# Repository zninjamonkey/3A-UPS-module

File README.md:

# 3A-UPS-module
made for hack club half life in 1 week. cut me some slack

This is supposed to be a UPS (uninterruptible power supply) module to power portable diy electronics projects.

It was inspired by the adafruit powerboost 1000c, but I wanted usb C connection and to be able to provide higher current to power devices such as a rapsberry pi.

It uses a BQ25306 for battery charging and load sharing, and a TPS61089 to boost the lithium ion battery to a 5V output. both chips are by Texas instruments. 

**kicad render**

<br>
**schematic**

<br>

I have not actually built this yet so I'm not sure if it even works

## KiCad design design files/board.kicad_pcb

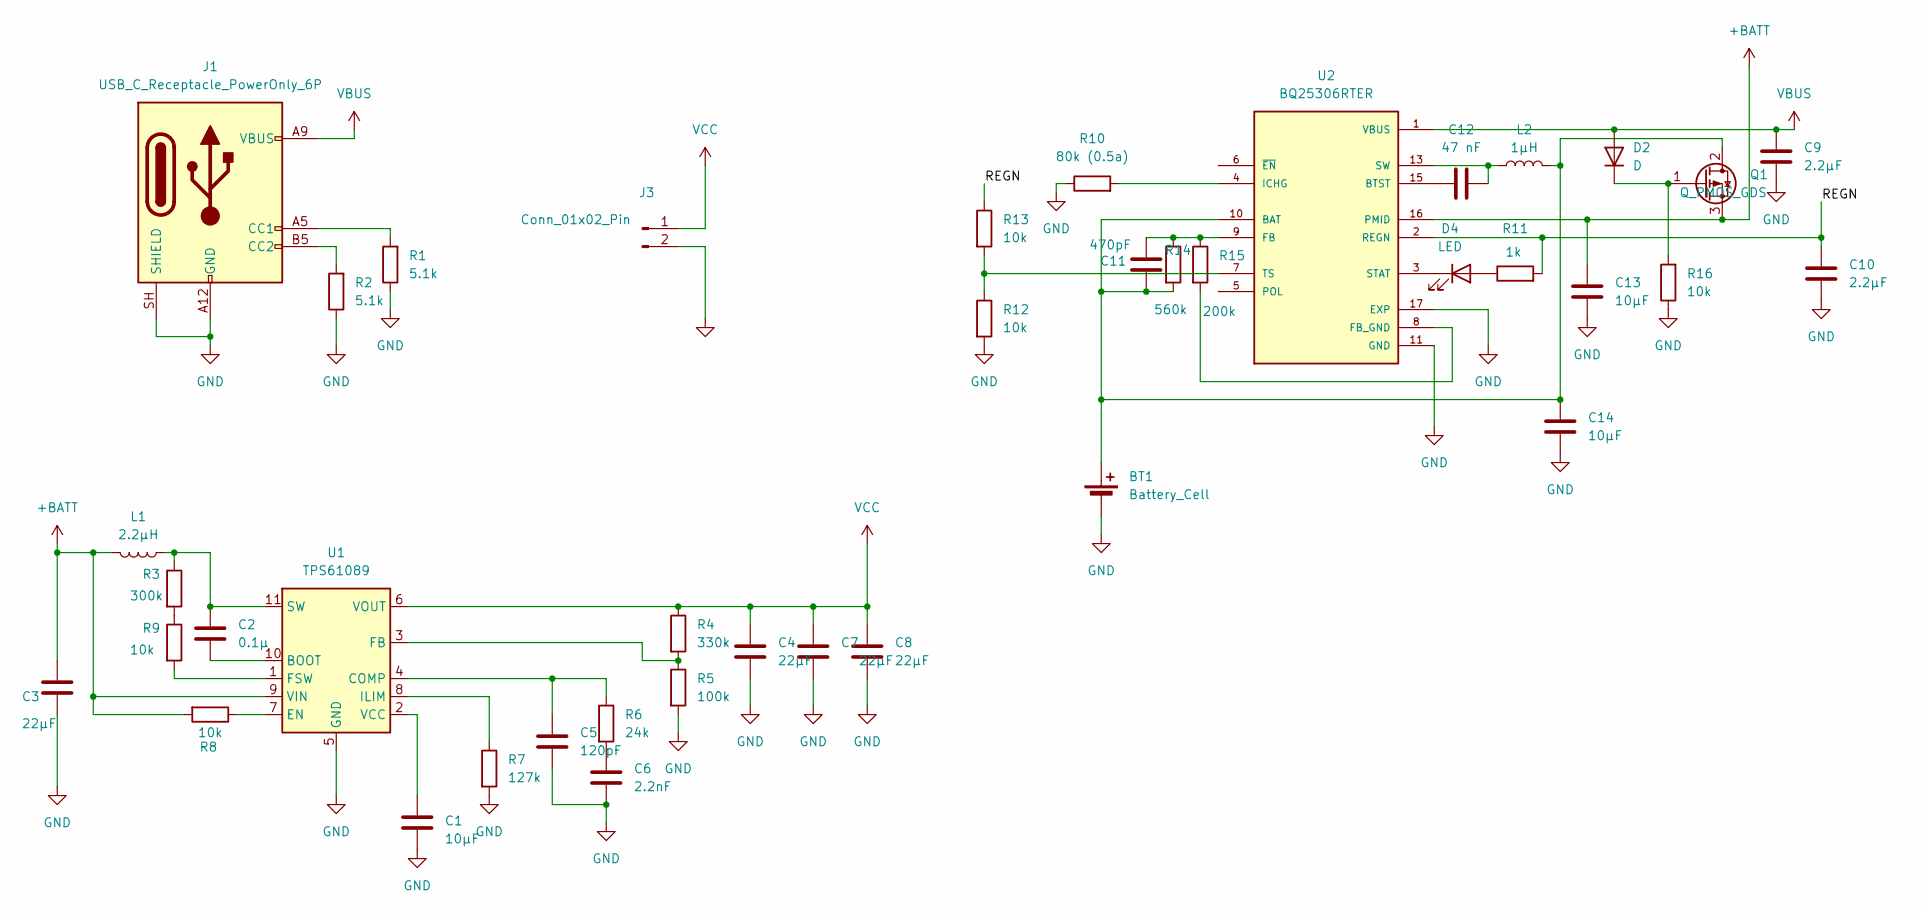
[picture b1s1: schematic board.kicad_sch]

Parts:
BT1: Battery_Cell; PinHeader_1x02_P2.54mm_Horizontal
C1: 10μF; C_1206_3216Metric
C2: 0.1μ; C_1206_3216Metric
C3, C4, C7, C8: 22μF; C_1206_3216Metric
C5: 120pF; C_1206_3216Metric
C6: 2.2nF; C_1206_3216Metric
C9, C10: 2.2µF; C_1206_3216Metric
C11: 470pF; C_1206_3216Metric
C12: 47 nF; C_1206_3216Metric
C13, C14: 10µF; C_1206_3216Metric
D2: D; D_SMA
D4: LED; LED_1206_3216Metric
J1: USB_C_Receptacle_PowerOnly_6P; USB_C_Receptacle_GCT_USB4125-xx-x_6P_TopMnt_Horizontal
J3: Conn_01x02_Pin; PinHeader_1x02_P2.54mm_Horizontal
L1: 2.2μH; L_6.3x6.3_H3
L2: 1µH; L_6.3x6.3_H3
Q1: Q_PMOS_GDS; SOT-23
R1, R2: 5.1k; R_1206_3216Metric
R3: 300k; R_1206_3216Metric
R4: 330k; R_1206_3216Metric
R5: 100k; R_1206_3216Metric
R6: 24k; R_1206_3216Metric
R7: 127k; R_1206_3216Metric
R8, R9, R12, R13, R16: 10k; R_1206_3216Metric
R10: 80k (0.5a); R_1206_3216Metric
R11: 1k; R_1206_3216Metric
R14: 560k; R_1206_3216Metric
R15: 200k; R_1206_3216Metric
U1: TPS61089; modified tps61089
U2: BQ25306RTER; IC_BQ25306RTER; PARTREV A

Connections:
+BATT: C3.1, C13.1, L1.2, Q1.3 (S), R8.2, U1.9 (VIN), U2.16 (PMID)
/REGN: C10.1, R11.2, R13.1, U2.2 (REGN)
GND: BT1.2 (-), C1.2, C3.2, C4.2, C5.2, C6.2, C7.2, C8.2, C9.2, C10.2, C13.2, C14.2, J1.A12 (GND), J1.B12 (GND), J1.SH (SHIELD), J3.2, R1.1, R2.1, R5.2, R7.2, R10.1, R12.2, R16.1, U1.5 (GND), U2.11 (GND), U2.12 (GND), U2.17 (EXP)
unnamed: BT1.1 (+), C11.1, C14.1, L2.2, Q1.2 (D), R14.2, U2.10 (BAT)
unnamed: C6.1, R6.2
unnamed: C12.2, L2.1, U2.13 (SW), U2.14 (SW)
unnamed: D2.1 (K), Q1.1 (G), R16.2
unnamed: D4.2 (A), R11.1
unnamed: D4.1 (K), U2.3 (STAT)
unnamed: J1.A5 (CC1), R1.2
unnamed: J1.B5 (CC2), R2.2
unnamed: R3.2, R9.1
unnamed: C2.2, U1.10 (BOOT)
unnamed: C5.1, R6.1, U1.4 (COMP)
unnamed: R8.1, U1.7 (EN)
unnamed: R4.2, R5.1, U1.3 (FB)
unnamed: R9.2, U1.1 (FSW)
unnamed: R7.1, U1.8 (ILIM)
unnamed: C2.1, L1.1, R3.1, U1.11 (SW)
unnamed: C1.1, U1.2 (VCC)
unnamed: C12.1, U2.15 (BTST)
unnamed: C11.2, R14.1, R15.1, U2.9 (FB)
unnamed: R15.2, U2.8 (FB_GND)
unnamed: R10.2, U2.4 (ICHG)
unnamed: R12.1, R13.2, U2.7 (TS)
VBUS: C9.1, D2.2 (A), J1.A9 (VBUS), J1.B9 (VBUS), U2.1 (VBUS)
VCC: C4.1, C7.1, C8.1, J3.1, R4.1, U1.6 (VOUT)

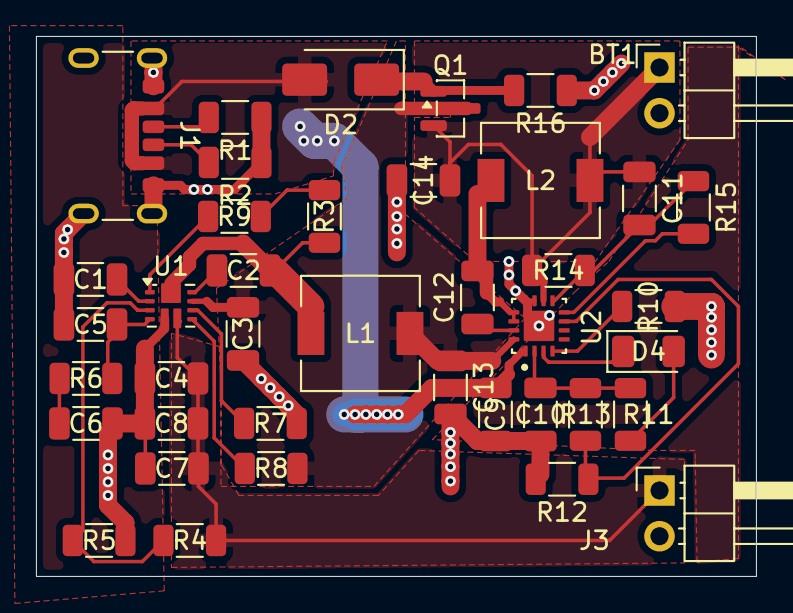
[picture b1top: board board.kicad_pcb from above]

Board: 2 copper layers, 40.0 x 30.0 mm, 40 parts (0 on the bottom side), 27 nets.

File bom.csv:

"Id";"Designator";"Footprint";"Quantity";"Designation";"Supplier and ref";
1;"BT1";"PinHeader_1x02_P2.54mm_Horizontal";1;"Battery_Cell";;;
2;"C1";"C_1206_3216Metric";1;"10μF";;;
3;"C2";"C_1206_3216Metric";1;"0.1μ";;;
4;"C3, C4, C7, C8";"C_1206_3216Metric";4;"22μF";;;
5;"C5";"C_1206_3216Metric";1;"120pF";;;
6;"C6";"C_1206_3216Metric";1;"2.2nF";;;
7;"C9, C10";"C_1206_3216Metric";2;"2.2µF";;;
8;"C11";"C_1206_3216Metric";1;"470pF";;;
9;"C12";"C_1206_3216Metric";1;"47 nF";;;
10;"C13, C14";"C_1206_3216Metric";2;"10µF";;;
11;"D2";"D_1206_3216Metric";1;"D";;;
12;"D4";"LED_1206_3216Metric";1;"LED";;;
13;"J1";"USB_C_Receptacle_GCT_USB4125-xx-x_6P_TopMnt_Horizontal";1;"USB_C_Receptacle_PowerOnly_6P";;;
14;"J3";"PinHeader_1x02_P2.54mm_Horizontal";1;"Conn_01x02_Pin";;;
15;"L1";"L_6.3x6.3_H3";1;"2.2μH";;;
16;"L2";"L_6.3x6.3_H3";1;"1µH";;;
17;"Q1";"SOT-23";1;"Q_PMOS_GDS";;;
18;"R1, R2";"R_1206_3216Metric";2;"5.1k";;;
19;"R3";"R_1206_3216Metric";1;"300k";;;
20;"R4";"R_1206_3216Metric";1;"330k";;;
21;"R5";"R_1206_3216Metric";1;"100k";;;
22;"R6";"R_1206_3216Metric";1;"24k";;;
23;"R7";"R_1206_3216Metric";1;"127k";;;
24;"R8, R9, R12, R13, R16";"R_1206_3216Metric";5;"10k";;;
25;"R10";"R_1206_3216Metric";1;"80k (0.5a)";;;
26;"R11";"R_1206_3216Metric";1;"1k";;;
27;"R14";"R_1206_3216Metric";1;"560k";;;
28;"R15";"R_1206_3216Metric";1;"200k";;;
29;"U1";"modified tps61089";1;"TPS61089";;;
30;"U2";"IC_BQ25306RTER";1;"BQ25306RTER";;;
